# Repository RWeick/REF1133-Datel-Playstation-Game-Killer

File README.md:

# REF1133-Datel-Playstation-Game-Killer
The Kicad files and eeprom dump of the Datel Game Killer for the Playstation.

I've also dumped and uploaded the memory card images presented by the Game Killer to the PSX. These contain the cheat saves created by Datel.

PCB Thickness: 0.8 mm

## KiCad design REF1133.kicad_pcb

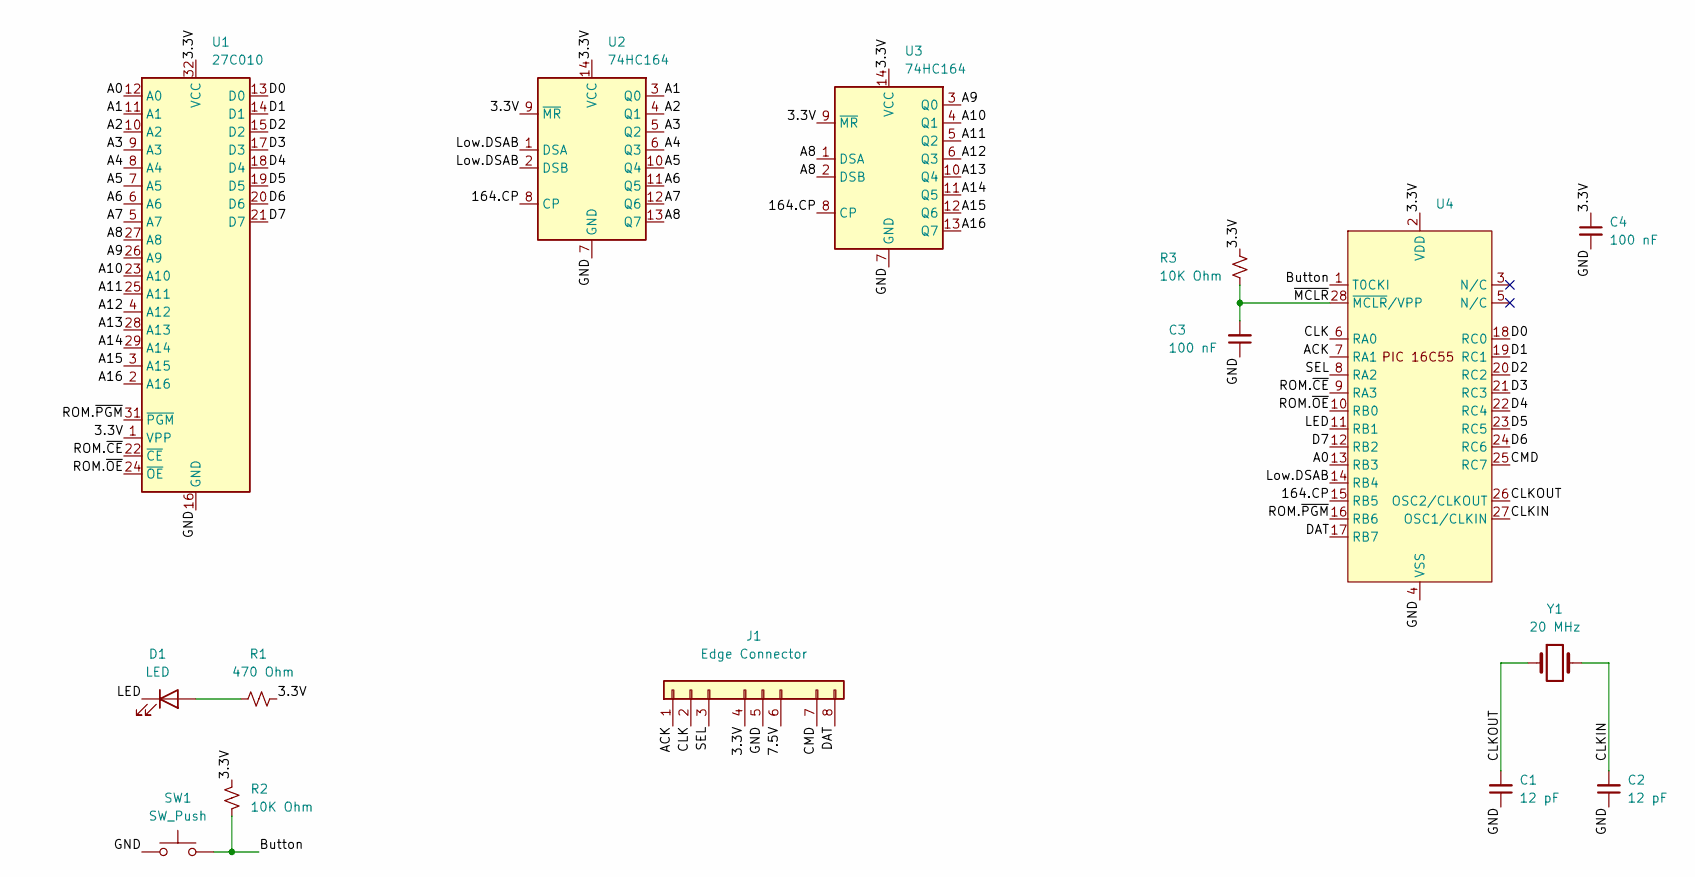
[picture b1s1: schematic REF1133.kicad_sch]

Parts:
C1, C2: 12 pF; SMD
C3, C4: 100 nF; SMD
D1: LED
J1: Edge Connector
R1: 470 Ohm; SMD
R2, R3: 10K Ohm; SMD
SW1: SW_Push; Button
U1: 27C010; NM27C010
U2, U3: 74HC164
U4: PIC 16C55
Y1: 20 MHz; Crystal

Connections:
/3.3V: C4.1, J1.4, R1.2, R2.2, R3.1, U1.1 (VPP), U1.32 (VCC), U2.9 (~MR), U2.14 (VCC), U3.9 (~MR), U3.14 (VCC), U4.2 (VDD)
/7.5V: J1.6
/164.CP: U2.8 (CP), U3.8 (CP), U4.15 (RB5)
/A0: U1.12 (A0), U4.13 (RB3)
/A1: U1.11 (A1), U2.3 (Q0)
/A2: U1.10 (A2), U2.4 (Q1)
/A3: U1.9 (A3), U2.5 (Q2)
/A4: U1.8 (A4), U2.6 (Q3)
/A5: U1.7 (A5), U2.10 (Q4)
/A6: U1.6 (A6), U2.11 (Q5)
/A7: U1.5 (A7), U2.12 (Q6)
/A8: U1.27 (A8), U2.13 (Q7), U3.1 (DSA), U3.2 (DSB)
/A9: U1.26 (A9), U3.3 (Q0)
/A10: U1.23 (A10), U3.4 (Q1)
/A11: U1.25 (A11), U3.5 (Q2)
/A12: U1.4 (A12), U3.6 (Q3)
/A13: U1.28 (A13), U3.10 (Q4)
/A14: U1.29 (A14), U3.11 (Q5)
/A15: U1.3 (A15), U3.12 (Q6)
/A16: U1.2 (A16), U3.13 (Q7)
/ACK: J1.1, U4.7 (RA1)
/Button: R2.1, SW1.2, U4.1 (T0CKI)
/CLK: J1.2, U4.6 (RA0)
/CLKIN: C2.2, U4.27 (OSC1/CLKIN), Y1.2
/CLKOUT: C1.2, U4.26 (OSC2/CLKOUT), Y1.1
/CMD: J1.7, U4.25 (RC7)
/D0: U1.13 (D0), U4.18 (RC0)
/D1: U1.14 (D1), U4.19 (RC1)
/D2: U1.15 (D2), U4.20 (RC2)
/D3: U1.17 (D3), U4.21 (RC3)
/D4: U1.18 (D4), U4.22 (RC4)
/D5: U1.19 (D5), U4.23 (RC5)
/D6: U1.20 (D6), U4.24 (RC6)
/D7: U1.21 (D7), U4.12 (RB2)
/DAT: J1.8, U4.17 (RB7)
/GND: C1.1, C2.1, C3.1, C4.2, J1.5, SW1.1, U1.16 (GND), U2.7 (GND), U3.7 (GND), U4.4 (VSS)
/LED: D1.1 (K), U4.11 (RB1)
/Low.DSAB: U2.1 (DSA), U2.2 (DSB), U4.14 (RB4)
/ROM.~CE: U1.22 (~CE), U4.9 (RA3)
/ROM.~OE: U1.24 (~OE), U4.10 (RB0)
/ROM.~PGM: U1.31 (~PGM), U4.16 (RB6)
/SEL: J1.3, U4.8 (RA2)
/~MCLR: C3.2, R3.2, U4.28 (~MCLR/VPP)
unnamed: D1.2 (A), R1.1

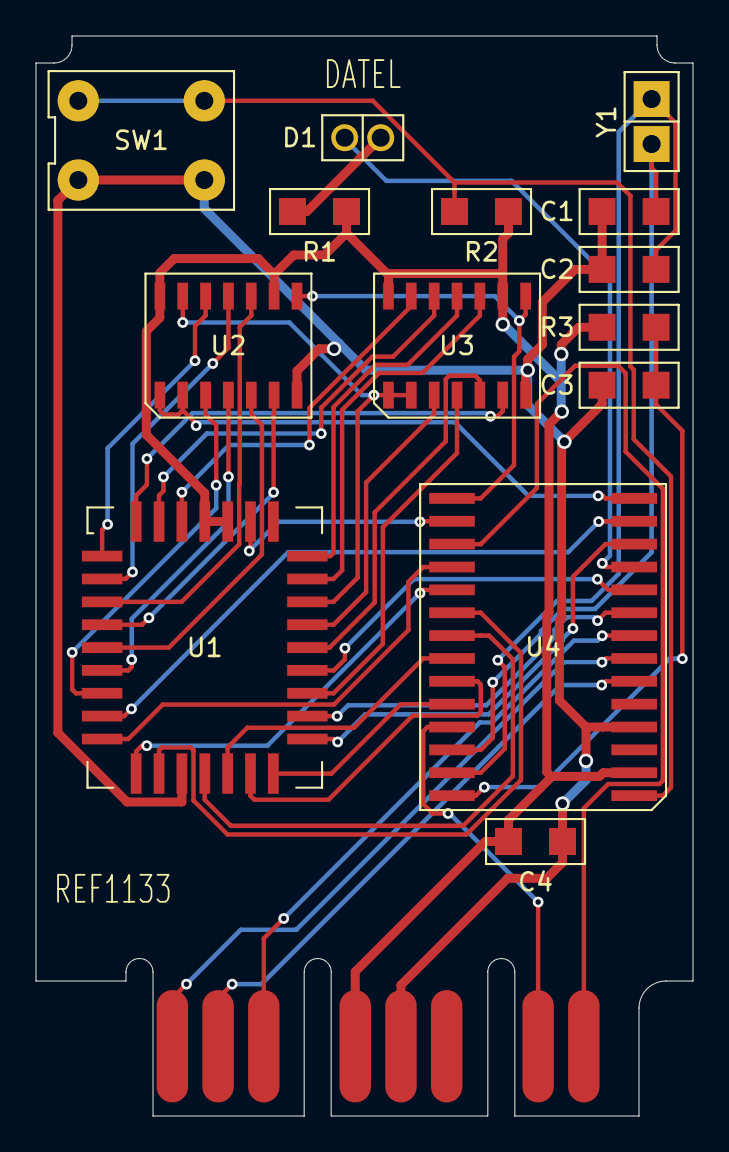
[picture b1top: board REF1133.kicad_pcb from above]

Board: 2 copper layers, 36.5 x 60.0 mm, 15 parts (0 on the bottom side), 43 nets.
